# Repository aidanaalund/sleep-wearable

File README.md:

# UT Austin ECE Senior Design Project: Sleep Monitoring Headband

## Description

This repository contains work on our sleep state tracker wearable headband for ECE Senior Design at UT Austin. Members are Aidan Aalund, Justin Banh, Alex Ho, and Kien Ton. Mentored by Dr. Edison Thomaz. The wearable is powered by a Nordic nRF54L15 module and uses an ADS1299 biosensing amplifier from Texas Instruments for the analog front end. Bluetooth low energy transmits EEG and motion features collected by the board to a mobile app, which runs a random forest model to identify the user's current sleep stage. The app shows trends over time, ratings of sleep quality, and gives tips for improvements.

To view the full PCB layout online, [go to KiCanvas!](https://kicanvas.org/?repo=https%3A%2F%2Fgithub.com%2Faidanaalund%2Fsleep-wearable%2Ftree%2Fmain%2Fwearable%2Fhw%2Fwearable)

## Repository Structure (WIP)

### Wearable device files (`./wearable`)

#### Hardware Files (`./wearable/hw`)

#### Software Files (`./wearable/sw`)

### Companion application files (`./reactNative`)

### Machine learning files (`./ml`)

#### Sleep Stage Classifier (`./ml/sleep`)

#### Meditation Classifier (`./ml/meditation`)

### Other documentation (`./documents`)

## Known Errata

- SWCLK and SWDIO labels are connected to the SWD header incorrectly in the schematic and layout

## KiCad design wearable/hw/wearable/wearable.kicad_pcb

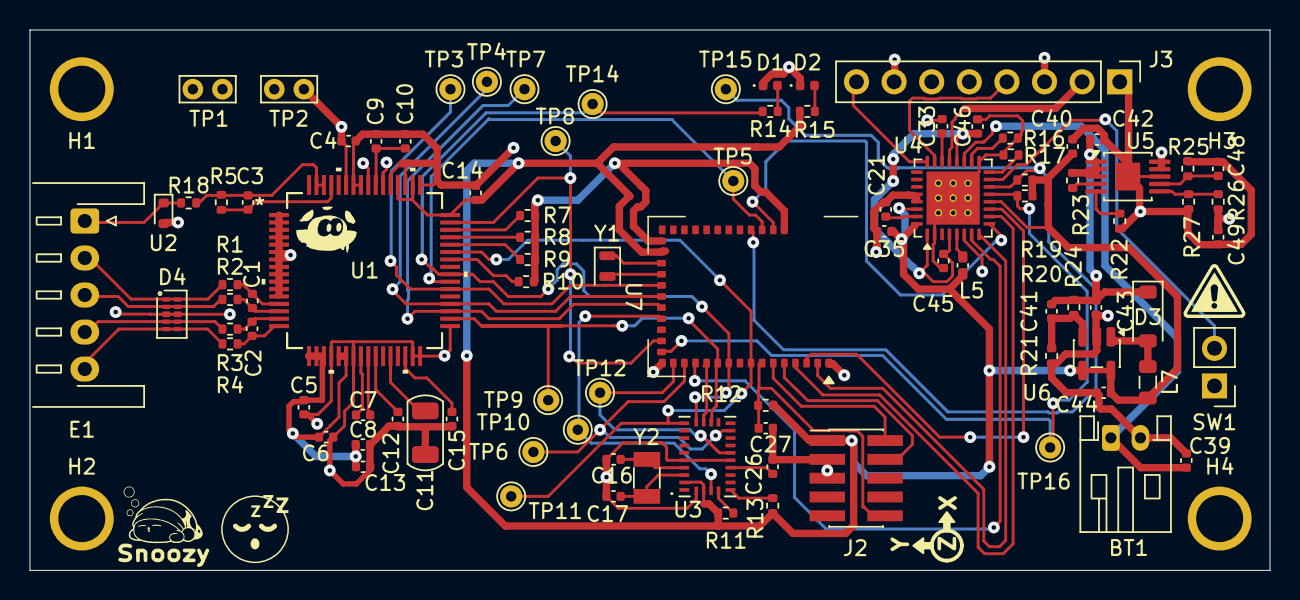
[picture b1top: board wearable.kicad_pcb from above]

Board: 4 copper layers, 83.8 x 36.5 mm, 97 parts (0 on the bottom side), 73 nets.

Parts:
BT1: 3.7V; JST_PH_S2B-PH-K_1x02_P2.00mm_Horizontal
C1, C2: 4.7nF; C_0402_1005Metric
C3: 1.5nF; C_0402_1005Metric
C4, C6, C10, C12, C13, C15, C21, C33: 1uF; C_0402_1005Metric
C5, C8, C14, C26: 0.1uF; C_0402_1005Metric
C7, C35, C40, C45, C46: 10uF; C_0402_1005Metric
C9: .1uF; C_0402_1005Metric
C11: 100uF; C_1206_3216Metric
C16, C17: 22pF; C_0402_1005Metric
C27: 3.9pF; C_0402_1005Metric
C39: 2.2uF; C_0402_1005Metric
C41: 3.3pF; C_0402_1005Metric
C42, C43, C44, C48, C49: 4.7uF; C_0402_1005Metric
D1, D2: LED; LED_0402_1005Metric
D3: MBR0530; D_SOD-123
D4: TPD4E05U06DQAR; USON-10_2.5x1.0mm_P0.5mm
E1: JST_XH_S5B-XH-A-1_1x05_P2.50mm_Horizontal
H1, H2, H3, H4: MountingHole_4_40
J2: Conn_02x05_Odd_Even; PinHeader_2x05_P1.27mm_Vertical_SMD
J3: USB-C Connector; PinHeader_1x08_P2.54mm_Vertical
L5: 2.2uH; L_0402_1005Metric_Pad0.77x0.64mm_HandSolder
L7: 6.8uH; L_0805_2012Metric
R1, R2, R3, R4, R7, R8, R9, R10, R11, R13, R18: 10K; R_0402_1005Metric
R5: 1M; R_0402_1005Metric
R12: 1K; R_0402_1005Metric
R14: 330; R_0402_1005Metric
R15: 820; R_0402_1005Metric
R16, R19, R20: 10k; R_0402_1005Metric
R17: 330k; R_0402_1005Metric
R21, R23: 200K; R_0402_1005Metric
R22: 499; R_0402_1005Metric
R24: 698k; R_0402_1005Metric
R25, R27: 49.9K; R_0402_1005Metric
R26: 453K; R_0402_1005Metric
SW1: PWR_Toggle; PinHeader_1x02_P2.54mm_Vertical
TP1: AVSS; TestPoint_Bridge_Pitch2.0mm_Drill0.7mm
TP2: AVDD; TestPoint_Bridge_Pitch2.0mm_Drill0.7mm
TP3, TP4, TP5, TP6, TP7, TP8, TP9, TP10, TP11, TP12, TP14, TP15, TP16: TP; TestPoint_THTPad_D1.5mm_Drill0.7mm
U1: ADS1299-4PAGR; PAG64_TEX
U2: TPD1E05U06DYA; D_SOD-523
U3: BNO086; IC_BNO080
U4: NPM1304-QEAA-R7; QFN-32-1EP_5x5mm_P0.5mm_EP3.6x3.6mm_ThermalVias_D3x3.00mm
U5: LT3042xMSE; MSOP-10-1EP_3x3mm_P0.5mm_EP1.68x1.88mm
U6: TPS61040DBV; SOT-23-5
U7: BL54L15-453-000xxx; BL54Lxx-LGA-39_14x10mm
Y1: 32.768kHz; Crystal_SMD_2012-2Pin_2.0x1.2mm
Y2: 32.768kHz; Crystal_SMD_3215-2Pin_3.2x1.5mm

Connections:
+3V3: C14.1, C35.1, C40.2, C44.1, J2.1, L5.1, L7.1, R11.1, R12.1, R13.1, R15.2, R19.1, R20.1, U1.48 (DVDD), U1.50 (DVDD), U1.52 (CLKSEL), U3.3 (VDD), U3.28 (VDDIO), U4.12 (VDDIO), U4.30 (LSIN2/VINLDO2), U4.32 (VOUT2), U6.4 (EN), U6.5 (VIN), U7.26 (VDD)
+5V3: C41.1, C42.1, C43.1, D3.1 (K), R23.1, R24.1, U5.1 (IN), U5.2 (IN), U5.3 (EN/UV)
+5V_USB: J3.2, U4.21 (VBUS)
/CAP: C26.1, U3.9 (CAP)
/XIN: C17.1, U3.27 (XIN32), Y2.1
/XOUT: C16.1, U3.26 (XOUT32/CLKSEL1), Y2.2
AVDD: C4.2, C5.1, C6.1, C8.1, C13.1, C49.1, R26.1, TP2.1, U1.1 (IN8N), U1.2 (IN8P), U1.3 (IN7N), U1.4 (IN7P), U1.5 (IN6N), U1.6 (IN6P), U1.7 (IN5N), U1.8 (IN5P), U1.9 (IN4N), U1.10 (IN4P), U1.11 (IN3N), U1.12 (IN3P), U1.17 (SRB1), U1.18 (SRB2), U1.19 (AVDD), U1.21 (AVDD), U1.22 (AVDD), U1.54 (AVDD1), U1.56 (AVDD), U1.59 (AVDD), U5.9 (OUTS), U5.10 (OUT)
AVSS: BT1.2 (-), C4.1, C5.2, C6.2, C8.2, C9.2, C10.2, C11.2, C12.2, C13.2, C14.2, C15.1, C16.2, C17.2, C21.2, C26.2, C27.2, C33.2, C35.2, C39.2, C40.1, C42.2, C43.2, C44.2, C45.2, C46.2, C48.2, C49.2, D1.1 (K), D2.1 (K), D4.3 (GND_1), D4.8 (GND_2), J2.3, J2.5, J3.1, J3.3, J3.7, R7.2, R8.2, R9.2, R10.2, R16.2, R17.2, R21.2, R22.2, R25.2, R27.2, SW1.1, TP1.1, U1.20 (AVSS), U1.23 (AVSS), U1.31 (RESV1), U1.32 (AVSS), U1.33 (DGND), U1.49 (DGND), U1.51 (DGND), U1.53 (AVSS1), U1.57 (AVSS), U1.58 (AVSS), U2.2 (GND), U3.2 (GND), U3.10 (CLKSEL0), U3.25 (GNDIO), U4.2 (PVSS1), U4.6 (PVSS2), U4.17 (VSET1), U4.28 (LSIN1/VINLDO1), U4.29 (LSOUT1/VOUTLDO1), U4.33 (AVSS), U5.8 (GND), U5.11 (GND), U6.2 (GND), U7.1 (VSS), U7.16 (VSS), U7.27 (VSS), U7.39 (VSS)
BOOT_BNO085: TP10.1, U3.4 (~BOOT), U7.20 (P1.07)
CS_ADS1299: TP5.1, U1.39 (*CS), U7.37 (P2.10)
CS_BNO085: U3.18 (~H_CS), U7.12 (P2.05)
DRDY: TP8.1, U1.47 (*DRDY), U7.18 (P0.01)
GPIO0: U4.7 (GPIO0), U7.13 (P2.03)
GPIO1: U4.8 (GPIO1), U7.2 (P2.09)
GPIO2: U4.9 (GPIO2), U7.38 (P2.06)
GPIO3: U4.10 (GPIO3), U7.4 (P2.07)
GPIO4: U4.11 (GPIO4), U7.3 (P2.08)
INT_BNO085: TP6.1, U3.14 (~H_INT), U7.14 (P1.03)
MISO: TP11.1, U1.43 (DOUT), U3.20 (H_SDA/H_MISO/TX), U7.8 (P2.02)
MOSI: TP9.1, U1.34 (DIN), U3.17 (SA0/H_MOSI), U7.11 (P2.04)
unnamed: BT1.1 (+), C39.1, U4.19 (VBAT)
unnamed: D1.2 (A), R14.1
unnamed: D2.2 (A), R15.1
unnamed: D3.2 (A), L7.2, U6.1 (SW)
unnamed: D4.1 (D1+), D4.10 (NC_4), E1.2 (D1+), R1.2
unnamed: D4.2 (D1-), D4.9 (NC_3), E1.3 (D1-), R2.2
unnamed: D4.4 (D2+), D4.7 (NC_2), E1.4 (D2+), R3.2
unnamed: D4.5 (D2-), D4.6 (NC_1), E1.5 (D2-), R4.2
unnamed: J3.4, U4.23 (CC1)
unnamed: J3.8, U4.24 (CC2)
unnamed: C3.1, R5.1, R18.2, U1.62 (BIASIN), U1.63 (BIASOUT)
unnamed: C3.2, R5.2, U1.61 (BIASINV)
unnamed: R10.1, U1.42 (GPIO1)
unnamed: R9.1, U1.44 (GPIO2)
unnamed: R8.1, U1.45 (GPIO3)
unnamed: R7.1, U1.46 (GPIO4)
unnamed: C2.2, R3.1, U1.15 (IN1N)
unnamed: C2.1, R4.1, U1.16 (IN1P)
unnamed: C1.2, R1.1, U1.13 (IN2N)
unnamed: C1.1, R2.1, U1.14 (IN2P)
unnamed: C11.1, U1.28 (VCAP1)
unnamed: C15.2, U1.30 (VCAP2)
unnamed: C9.1, C10.1, U1.55 (VCAP3)
unnamed: C12.1, U1.26 (VCAP4)
unnamed: C7.2, U1.25 (VREFN)
unnamed: C7.1, U1.24 (VREFP)
unnamed: R13.2, U3.6 (PS0/WAKE)
unnamed: R11.2, U3.5 (PS1)
unnamed: C21.1, U4.31 (LSOUT2/VOUTLDO2)
unnamed: R16.1, U4.18 (NTC)
unnamed: SW1.2, U4.15 (SHPHLD)
unnamed: L5.2, U4.5 (SW2)
unnamed: C33.1, U4.22 (VBUSOUT)
unnamed: R17.1, U4.16 (VSET2)
unnamed: R22.1, U5.5 (ILIM)
unnamed: R23.2, U5.4 (PG)
unnamed: R26.2, R27.1, U5.6 (PGFB)
unnamed: C48.1, R25.1, U5.7 (SET)
unnamed: C41.2, R21.1, R24.2, U6.3 (FB)
unnamed: U7.25 (P1.00), Y1.1
unnamed: U7.24 (P1.01), Y1.2
PWDWN_ADS1299: TP7.1, U1.35 (*PWDN), U7.21 (P1.06)
RESET: C27.1, J2.10, R12.2, U7.7 (~RESET)
RST_ADS1299: TP4.1, U1.36 (*RESET), U7.22 (P1.05)
RST_BNO085: TP12.1, U3.11 (~RST), U7.15 (P1.02)
SCK: R14.2, TP14.1, U1.40 (SCLK), U3.19 (H_SCL/SCK/RX), U7.10 (P2.01)
SCL: R19.2, TP15.1, U4.14 (SCL), U7.36 (P0.03)
SDA: R20.2, TP16.1, U4.13 (SDA), U7.17 (P0.00)
START_ADS1299: TP3.1, U1.38 (START), U7.23 (P1.04)
SWDCLK: J2.4, U7.6 (SWDCLK)
SWDIO: J2.2, U7.5 (SWDIO)
VBIAS: E1.1 (Bias), R18.1, U2.1 (I/O)
VSYS: C45.1, C46.1, U4.1 (VOUT1), U4.4 (PVDD), U4.20 (VSYS)

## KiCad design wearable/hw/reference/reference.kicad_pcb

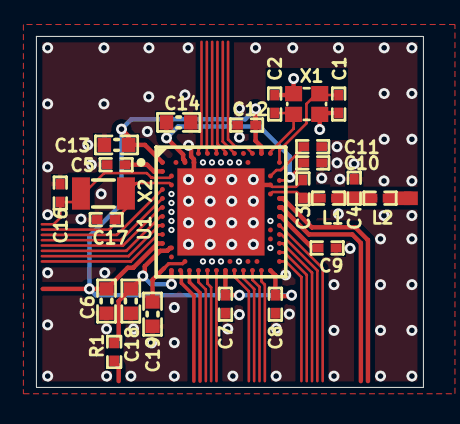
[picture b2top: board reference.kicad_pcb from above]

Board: 4 copper layers, 21.5 x 19.5 mm, 24 parts (0 on the bottom side), 14 nets.

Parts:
C1, C2, C16, C17: 12pF; CAPC1005X04L
C3: 1.0pF; CAPC1005X04L
C4: 1.2pF; CAPC1005X04L
C5, C7, C8, C12: 100nF; CAPC1005X04L
C6, C18, C19: 4.7µF; CAPC1608X06L
C9: 820pF; CAPC1005X04L
C10: N.C.; CAPC1005X04L
C11: 100pF; CAPC1005X04L
C13, C14: 1.0µF; CAPC1608X06L
L1: 4.7nH; INDC1005X04L
L2: 2.2nH; INDC1005X04L
R1: 2R2; RESC1005X04L
U1: nRF52833-QIAA; AQFN50P700X700X85_HS-74N
X1: 32MHz; BT-XTAL_2016
X2: 32.768kHz; XTAL_3215

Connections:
DEC1: C5.1, U1.C1
DEC3: C11.1, U1.D23
DEC4_6: C10.2, C14.2, U1.B5, U1.E24
GND: C1.2, C2.2, C3.1, C4.1, C5.2, C6.2, C7.2, C8.2, C9.2, C10.1, C11.2, C12.2, C13.2, C14.1, C16.2, C17.2, C18.2, C19.2, U1.74, U1.B7, U1.F23, X1.2, X1.4
NetC3_2: C3.2, L1.1, U1.H23
NetC4_2: C4.2, L1.2, L2.1
NetC9_1: C9.1, U1.N24
NetC19_1: C19.1, U1.AC5
P0.00/XL1: C16.1, U1.D2, X2.1
P0.01/XL2: C17.1, U1.F2, X2.2
VBUS_nRF: C18.1, R1.2, U1.AD2, U1.Y2
VDD_NRF: C6.1, C7.1, C8.1, C12.1, C13.1, U1.A22, U1.AD14, U1.AD23, U1.B1, U1.W1
XC1: C1.1, U1.B24, X1.1
XC2: C2.1, U1.A23, X1.3

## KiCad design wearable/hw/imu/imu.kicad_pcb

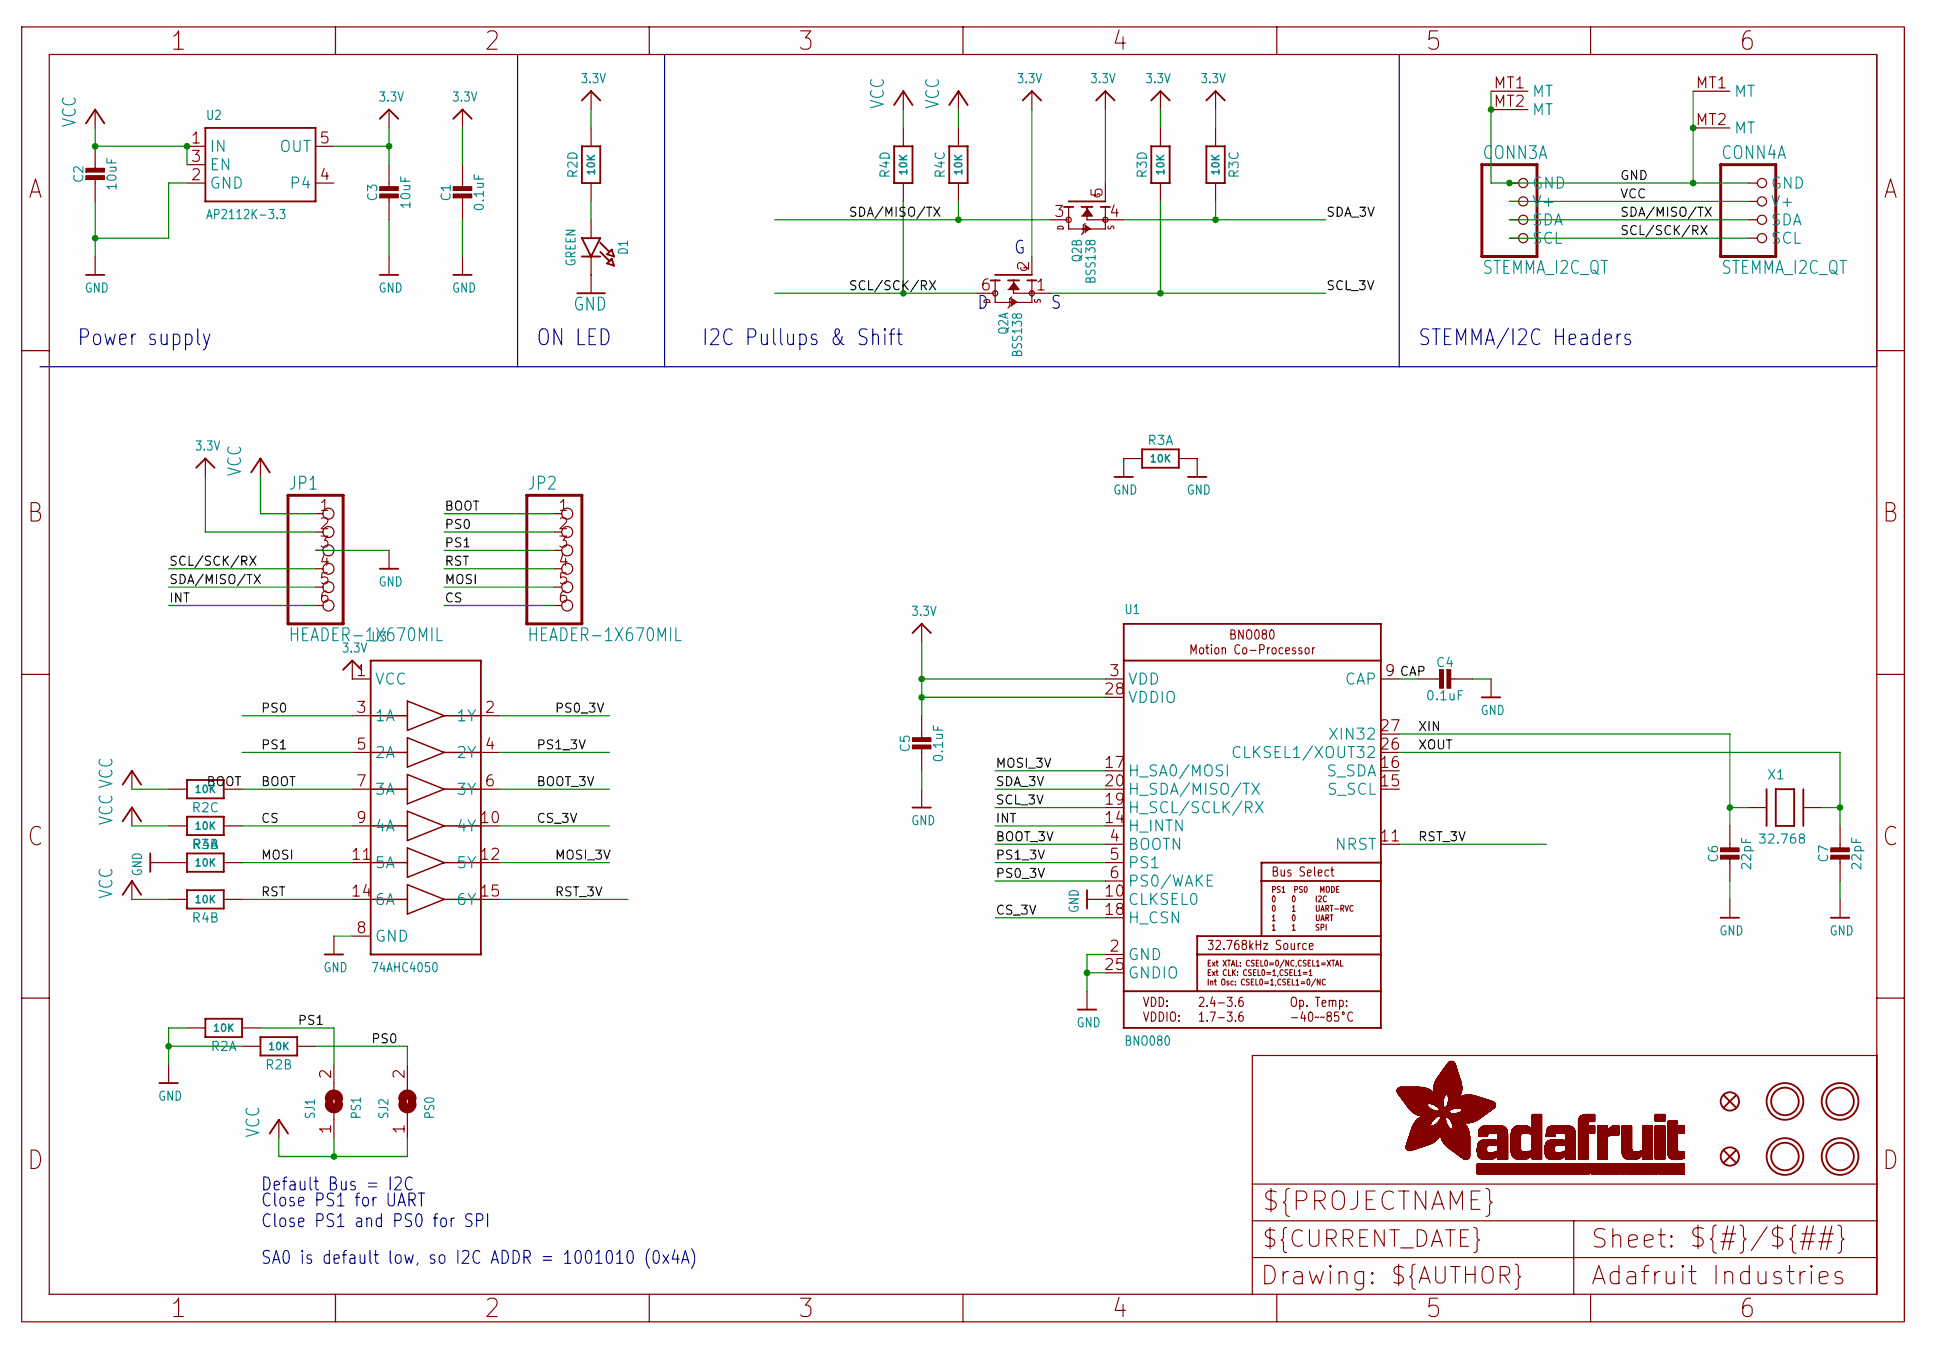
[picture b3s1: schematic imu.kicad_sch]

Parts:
C1, C4, C5: 0.1uF; 0603-NO
C2, C3: 10uF; 0805-NO
C6, C7: 22pF; 0603-NO
CONN3, CONN4: STEMMA_I2C_QT; JST_SH4
D1: GREEN; CHIPLED_0603_NOOUTLINE
FID3, FID4: FIDUCIAL_1MM
JP1, JP2: HEADER-1X670MIL; 1X06_ROUND_70
Q2: BSS138; SOT363
R2, R3, R4: 10K; RESPACK_4X0603
SJ1: PS1; SOLDERJUMPER_ARROW_NOPASTE
SJ2: PS0; SOLDERJUMPER_ARROW_NOPASTE
U1: BNO080
U2: AP2112K-3.3; SOT23-5
U3: 74AHC4050; TSSOP16
U$1, U$17, U$19, U$21: MOUNTINGHOLE2.5; MOUNTINGHOLE_2.5_PLATED
X1: 32.768; XTAL3215

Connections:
3.3V: C1.1, C3.1, C5.1, JP1.2, Q2.2 (G), Q2.5 (G), R2.5 (2), R3.3 (1), R3.5 (2), U1.3 (VDD), U1.28 (VDDIO), U2.5 (OUT), U3.1 (VCC)
BOOT: JP2.1, R2.3 (1), U3.7 (3A)
BOOT_3V: U1.4 (BOOTN), U3.6 (3Y)
CAP: C4.2, U1.9 (CAP)
CS: JP2.6, R4.1, U3.9 (4A)
CS_3V: U1.18 (H_CSN), U3.10 (4Y)
GND: C1.2, C2.2, C3.2, C4.1, C5.2, C6.2, C7.2, CONN3.1 (GND), CONN3.MT1 (MT), CONN3.MT2 (MT), CONN4.1 (GND), CONN4.MT1 (MT), CONN4.MT2 (MT), D1.C, JP1.3, R2.7 (2), R2.8 (2), R3.1, R3.2 (1), R3.8 (2), U1.2 (GND), U1.10 (CLKSEL0), U1.25 (GNDIO), U2.2 (GND), U3.8 (GND)
INT: JP1.6, U1.14 (H_INTN)
MOSI: JP2.5, R3.7 (2), U3.11 (5A)
MOSI_3V: U1.17 (H_SA0/MOSI), U3.12 (5Y)
unnamed: D1.A, R2.4 (1)
PS0: JP2.2, R2.2 (1), SJ2.2, U3.3 (1A)
PS0_3V: U1.6 (PS0/WAKE), U3.2 (1Y)
PS1: JP2.3, R2.1, SJ1.2, U3.5 (2A)
PS1_3V: U1.5 (PS1), U3.4 (2Y)
RST: JP2.4, R4.2 (1), U3.14 (6A)
RST_3V: U1.11 (NRST), U3.15 (6Y)
SCL/SCK/RX: CONN3.4 (SCL), CONN4.4 (SCL), JP1.4, Q2.6 (D), R4.4 (1)
SCL_3V: Q2.1 (S), R3.4 (1), U1.19 (H_SCL/SCLK/RX)
SDA/MISO/TX: CONN3.3 (SDA), CONN4.3 (SDA), JP1.5, Q2.3 (D), R4.3 (1)
SDA_3V: Q2.4 (S), R3.6 (2), U1.20 (H_SDA/MISO/TX)
VCC: C2.1, CONN3.2 (V+), CONN4.2 (V+), JP1.1, R2.6 (2), R4.5 (2), R4.6 (2), R4.7 (2), R4.8 (2), SJ1.1, SJ2.1, U2.1 (IN), U2.3 (EN)
XIN: C6.1, U1.27 (XIN32), X1.P$1
XOUT: C7.1, U1.26 (CLKSEL1/XOUT32), X1.P$2

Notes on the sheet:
SA0 is default low, so I2C ADDR = 1001010 (0x4A)
Default Bus = I2C
STEMMA/I2C Headers
I2C Pullups & Shift
Power supply
ON LED
Close PS1 for UART Close PS1 and PS0 for SPI

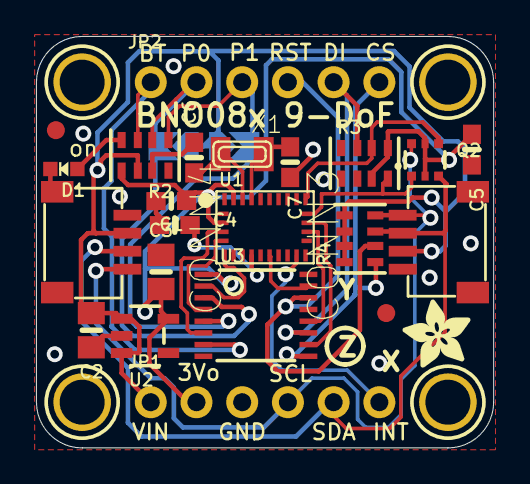
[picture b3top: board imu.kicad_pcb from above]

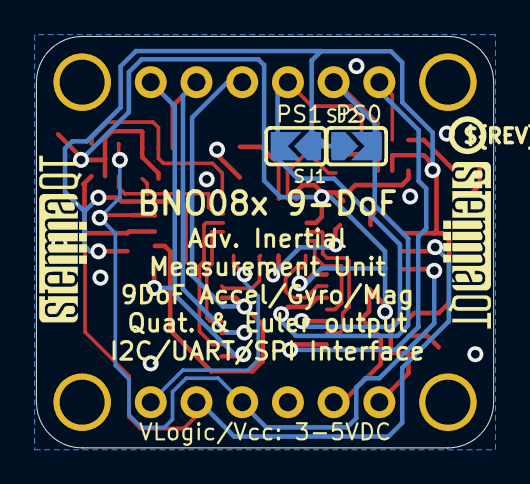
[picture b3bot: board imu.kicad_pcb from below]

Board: 2 copper layers, 25.4 x 22.9 mm, 32 parts (5 on the bottom side), 24 nets.

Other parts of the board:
U$22: ADAFRUIT_3.5MM
U$25: PCBFEAT-REV-040
U$30, U$31: STEMMAQT

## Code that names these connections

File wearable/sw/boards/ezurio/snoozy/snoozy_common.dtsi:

/*
 * Copyright (c) 2024 Nordic Semiconductor ASA
 * Copyright (c) 2025 Ezurio LLC
 *
 * SPDX-License-Identifier: Apache-2.0
 */

#include "snoozy_nrf54l_10_15-pinctrl.dtsi"

/ {
    aliases {
        ads1299 = &ads1299;
        bno086 = &bno086;
        npm1304 = &npm1304;
    };
};

&spi20 {
    status = "okay";
    cs-gpios =  <&gpio2 10 GPIO_ACTIVE_LOW>, // TODO: do these map to ads and bno respectively? 
                <&gpio2 5 GPIO_ACTIVE_LOW>;

    ads1299: ads1299@0 {
        compatible = "ti,ads1299";          /* custom binding you'll define */
        reg = <0>;                           /* index into cs-gpios */
        spi-max-frequency = <4000000>;       /* ADS1299 max 4 MHz */
        label = "ADS1299";
        start-gpios = <&gpio1 4 GPIO_ACTIVE_LOW>;
        rst-gpios = <&gpio1 5 GPIO_ACTIVE_LOW>;
        pwdwn-gpios = <&gpio1 6 GPIO_ACTIVE_LOW>;
        drdy-gpios = <&gpio0 1 GPIO_ACTIVE_LOW>;
    };

    bno086: bno086@1 {
        compatible = "ceva,bno086";          /* custom binding you'll define */
        reg = <1>;                           /* index into cs-gpios */
        spi-max-frequency = <3000000>;       /* BNO086 max 3 MHz */
        label = "BNO086";
        int-gpios = <&gpio1 3 GPIO_ACTIVE_LOW>;
        rst-gpios = <&gpio1 2 GPIO_ACTIVE_LOW>;
        boot-gpios = <&gpio1 7 GPIO_ACTIVE_LOW>;
    };
};
/delete-node/ &{/pin-controller/uart20_default/group1/};
/delete-node/ &{/pin-controller/uart20_default/group2/};

&i2c22 {
    status = "okay";    /* enable the I2C bus */
    pinctrl-0 = <&i2c22_default>;
    pinctrl-names = "default";
    npm1304: pmic@6b {
        label = "npm1304";
        gpio-controller;
        compatible = "nordic,npm1304";
        reg = <0x6b>;

        regulators {
            ldo2: LDO2 {
                regulator-init-microvolt = <3000000>;
                regulator-boot-on;
            };

            pvss2: PVSS2 {
                regulator-boot-on;
            };
        };
        #gpio-cells = <2>;
    };

    clock-frequency = <I2C_BITRATE_STANDARD>;
};

/ {
    zephyr,user {
        // pmic-gpios = <&pmic 0 0>; // TODO: if we need to use pmic gpio in app, instantiate them here.
        ads_reset_gpios = <&gpio1 5 GPIO_ACTIVE_LOW>;
        ads_start_gpios = <&gpio1 4 GPIO_ACTIVE_LOW>;
        ads_drdy_gpios  = <&gpio0 1 GPIO_ACTIVE_LOW>;  /* replace X with your DRDY pin */
        ads_pwdwn_gpios = <&gpio1 6 GPIO_ACTIVE_LOW>;
    };
};


&pinctrl {
    spi20_default: spi20_default {
        group1 {
            psels = <NRF_PSEL(SPIM_SCK, 2, 1)>,
                    <NRF_PSEL(SPIM_MISO, 2, 2)>,
                    <NRF_PSEL(SPIM_MOSI, 2, 4)>;
            nordic,drive-mode = <NRF_DRIVE_H0H1>;
            bias-disable;
        };
    };
    i2c22_default: i2c22_default {
        group1 {
            psels = <NRF_PSEL(TWIM_SCL, 0, 3)>, <NRF_PSEL(TWIM_SDA, 0, 0)>;
        };
    };
};

/* BLE things. May not work outside of NUS example. */

// &uart20 {
// 	current-speed = <115200>;
// 	pinctrl-0 = <&uart20_default>;
// 	pinctrl-1 = <&uart20_sleep>;
// 	pinctrl-names = "default", "sleep";
// };

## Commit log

2025-10-21 Added dataset testing notebook
2025-10-22 Dataset accessible as pandas dataframe
2025-10-22 Updated .gitignore
2025-10-22 Accessing datasets properly
2025-10-22 Added ML section (TODO)
2025-10-22 reactNative
2025-10-28 Changed to Nordic UART Service (NUS) example
2025-10-29 Added KiCAD project and modified SW starter code
2025-10-29 Pushed new gitignore
2025-10-29 gitignore updated again
2025-10-29 Added symbols and stuff to library
2025-10-30 Updated schematic with needed parts
2025-10-31 Added 445L footprints/symbols and changed some stuff
2025-11-02 Added draw.io diagram to docs
2025-11-09 wearable
2025-11-09 Changed git ignore
2025-11-09 Fixing some stuff
2025-11-09 Add peripheral UART source code
2025-11-09 Updated gitignore
2025-11-09 Updated .gitignore to ignore build files
2025-11-09 Remove build artifacts from tracking and update gitignore
2025-11-09 Ignore boards directories
2025-11-09 Finally
2025-11-09 Handoff to kien
2025-11-10 Deleted files
2025-11-10 Added gitignore
2025-11-10 change
2025-11-10 Fixed all the jank in build
2025-11-17 SPI api include
2025-11-30 WIP final schematic
2025-11-30 Done with M3 schematic
2025-12-01 Moved around some stuff
2025-12-18 HW v1 complete
2025-12-19 HW v1 passes ERC
2025-12-19 Starting footprint assignments
2025-12-27 Big stuff
2026-01-08 Added 54LDK build
2026-01-12 Started early version of layout
2026-01-12 Starting to layout nrf54L15
2026-01-13 Placed a bunch of stuff
2026-01-13 Getting there
2026-01-14 More layout progress and some fun stuff
2026-01-14 Some more changes
2026-01-14 Added snoozy submodule
2026-01-14 Working with submodule stuff
2026-01-14 Some stuff
2026-01-14 Something with submodules
2026-01-14 Ground pours and more routing
2026-01-15 Significant layout progress
    NOTE: We will need to rework the power management portion of the schematic due to layout issues
2026-01-15 Schematic of new power setup done
2026-01-15 Slop layout for new power block
2026-01-17 Questioning life choices
2026-01-17 Finished routing (mostly) + better testpoints
2026-01-18 Ready for review
2026-01-21 Gerbers
2026-01-21 Example for Alex
2026-01-21 leaky
2026-01-22 BL54L15 added
2026-01-26 Ready for design review
2026-01-28 Checking with Alex
2026-01-28 Almost done with design review...
2026-01-28 Design review DONE
2026-01-30 Layed out design review changes
2026-02-01 Added BoM for M1 prototype
2026-02-02 ESD protection, cyton reference, silkscreen update
2026-02-02 hole cad
2026-02-02 Printout documents, reworked analog inputs
2026-02-02 yaas
2026-02-03 Demo FW complete, PCB layout finalized (awaiting review from staff)
2026-02-03 Prototype schematic done, organize repo a bit
2026-02-03 Improved design guide
2026-02-04 ready for m1
2026-02-06 Prepping for ordering everything
2026-02-09 Unpatched cheap PCB glitch
2026-02-09 snoozy_final
2026-02-09 Prep for JLC
2026-02-11 Passes JLCPCB DRU file
2026-02-11 Board ordered
2026-02-11 firmware drawing
2026-02-16 snoozy_final submodule
2026-02-16 fixed gitmodules
2026-02-16 added files for system
2026-02-18 pmic devicetree
2026-03-04 pcb step file for case cad
2026-03-04 configured devicetree for imu and adc
2026-03-17 Forgot to apply stash
2026-03-19 reactNatibve
2026-03-24 POC of ML
2026-03-25 Updated backups
2026-03-25 onnx
2026-03-30 Added toggle button model
2026-03-30 moved cad files
2026-04-01 Auto stash before merge of "main" and "origin/main"
2026-04-01 snoozy final helmet cad file
2026-04-01 model now multimodal
2026-04-04 Fixed name on PCB silk
2026-04-04 multimodal onnx files
2026-04-05 npm1304
2026-04-06 moved npm13xx_one_button
2026-04-08 appIcon
2026-04-08 snoozy_final changes
2026-04-09 icon
2026-04-10 Documented SWD connector pin mismatch
2026-04-10 Snoozy is a board now
2026-04-11 Improved snoozy board files
2026-04-12 meditation onnx created
2026-04-13 Submodule update
2026-04-13 Device tree update
2026-04-15 Helmet CAD files
2026-04-15 LaTeX WIP drawings, renders, and minor changes
2026-04-15 spi debug
2026-04-16 debug attempt
2026-04-16 fused model v4
2026-04-16 Starting meditation...
2026-04-17 Confusion Matrix decent
2026-04-17 Meditation outline
2026-04-18 Little stuff
2026-04-18 Call me a machine the way I'm learning
2026-04-18 Some meditation improvements
2026-04-19 Test data
2026-04-20 onnxWorking
2026-04-21 4/20
2026-04-21 test gpios
2026-04-21 bno 4/21
2026-04-22 BLtest
2026-04-24 4/24 cry
2026-04-25 EEGNet WIP
2026-04-26 4/25
2026-04-26 NNAPI
2026-04-26 thoughts and prayers
2026-04-26 up down UP DOWN!
2026-04-26 Documentation
2026-04-26 Moved docs
2026-04-26 4/26
2026-04-26 Out of time...
2026-04-26 Final header
2026-04-27 prayers no thoughts
2026-04-27 corrected array transmission
2026-04-27 BLcircle
2026-04-27 new snippet
2026-04-27 working
2026-04-27 numCircle
2026-04-28 Final pre-recorded data
2026-04-28 Gitignore updated
2026-04-28 Renaming files
2026-04-28 Cleaned up repo structure
2026-04-28 More cleaning of repo structure
2026-04-30 Removed .gcode files
